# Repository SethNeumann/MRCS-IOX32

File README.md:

# MRCS-IOX32

## License: Creative Commons Attribution-NonCommercial-ShareAlike

MRCS I2C IO expander for use with cpNode CMRI nodes.

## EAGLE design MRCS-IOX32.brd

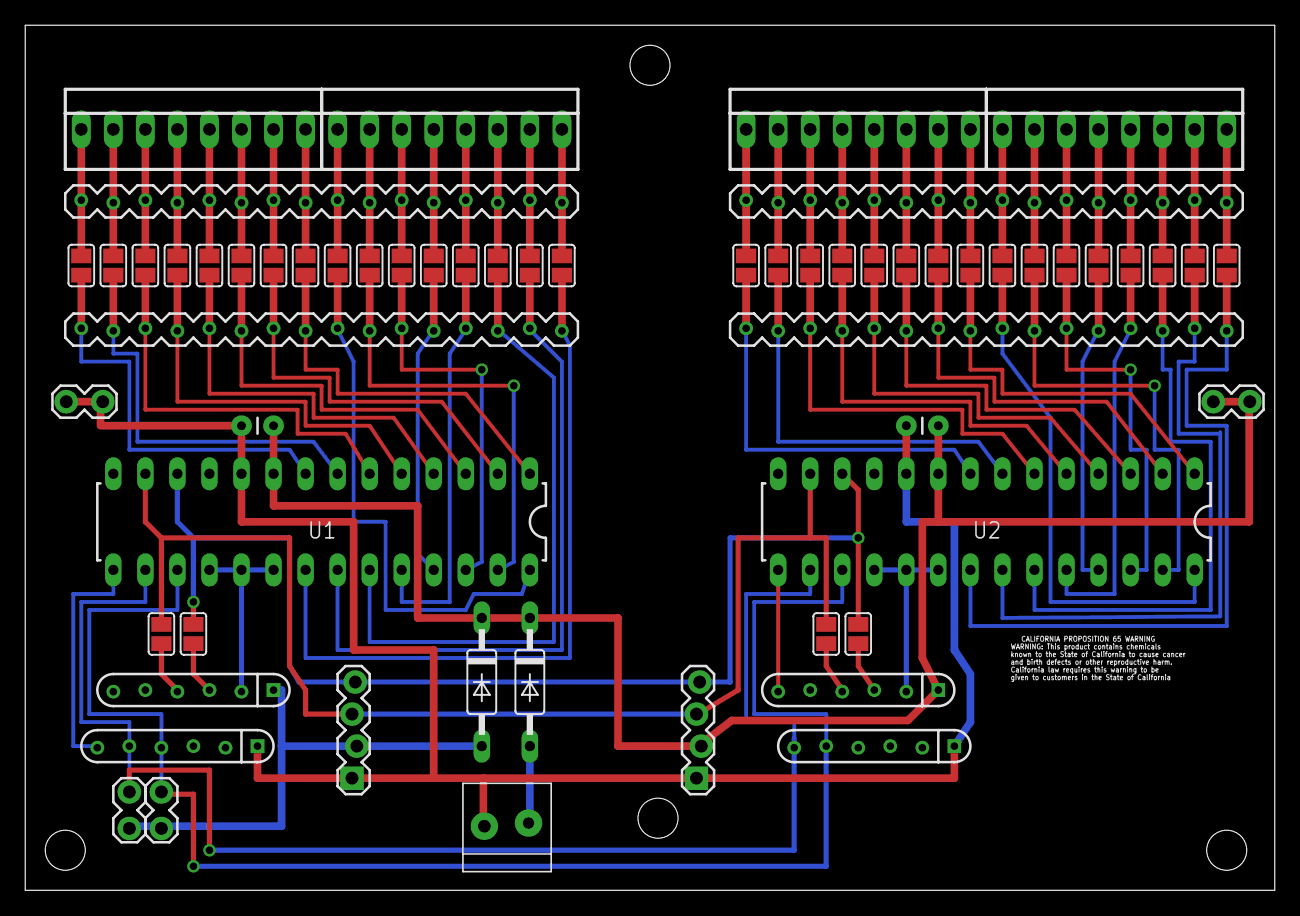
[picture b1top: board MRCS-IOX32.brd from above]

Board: 2 copper layers, 99.1 x 68.6 mm, 67 parts (0 on the bottom side), 4 nets.

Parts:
5V: 1X02_LOCK
ADDR1, ADDR2: 1X02_LOCK
C1, C2: .01uf; CAP-PTH-SMALL
COM: 1X02_LOCK
D1: D1; C2992
D2: D2; C2992
E$1, E$6, E$7, E$8: DRILL_0.1250
E$9: MRCSLOGOTOP
E$10, E$19: 1X04_LOCK
E$12, E$13, E$15, E$25: 1X16_MACHINE-PIN-HEADER_LOCK.004
E$14: CA-PROP65WARNING
EXT5V: 3.5MMTERM
I2CT1, I2CT2, I2CT3, I2CT4: 2P-SMD-2X3.3
PORTA, PORTA1: 22-23-2081
PORTB, PORTB1: 22-23-2081
RP1, RP2, RP3, RP4: RPACK-SIP-PTH-5
SJ1, SJ2, SJ3, SJ4, SJ5, SJ6, SJ7, SJ8, SJ9, SJ10, SJ11, SJ12, SJ13, SJ14, SJ15, SJ16, SJ17, SJ18, SJ19, SJ20, SJ21, SJ22, SJ23, SJ24, SJ25, SJ26, SJ27, SJ28, SJ29, SJ30, SJ31, SJ32: 2P-SMD-2X3.3
U1, U2: MCP23017; DIL28-3

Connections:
S$7: U1.18, U1.19, U1.20
S$73: U1.12, U2.12
S$74: U2.18, U2.19, U2.20
S$79: C1.1, C2.1, U1.9, U2.9

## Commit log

2019-12-03 add to git
2019-12-03 doc.md
2019-12-03 put real content in doc

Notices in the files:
parts and their libraries:
SparkFun-Connectors: Licensing: CC v3.0 Share-Alike You are welcome to use this library for commercial purposes.
